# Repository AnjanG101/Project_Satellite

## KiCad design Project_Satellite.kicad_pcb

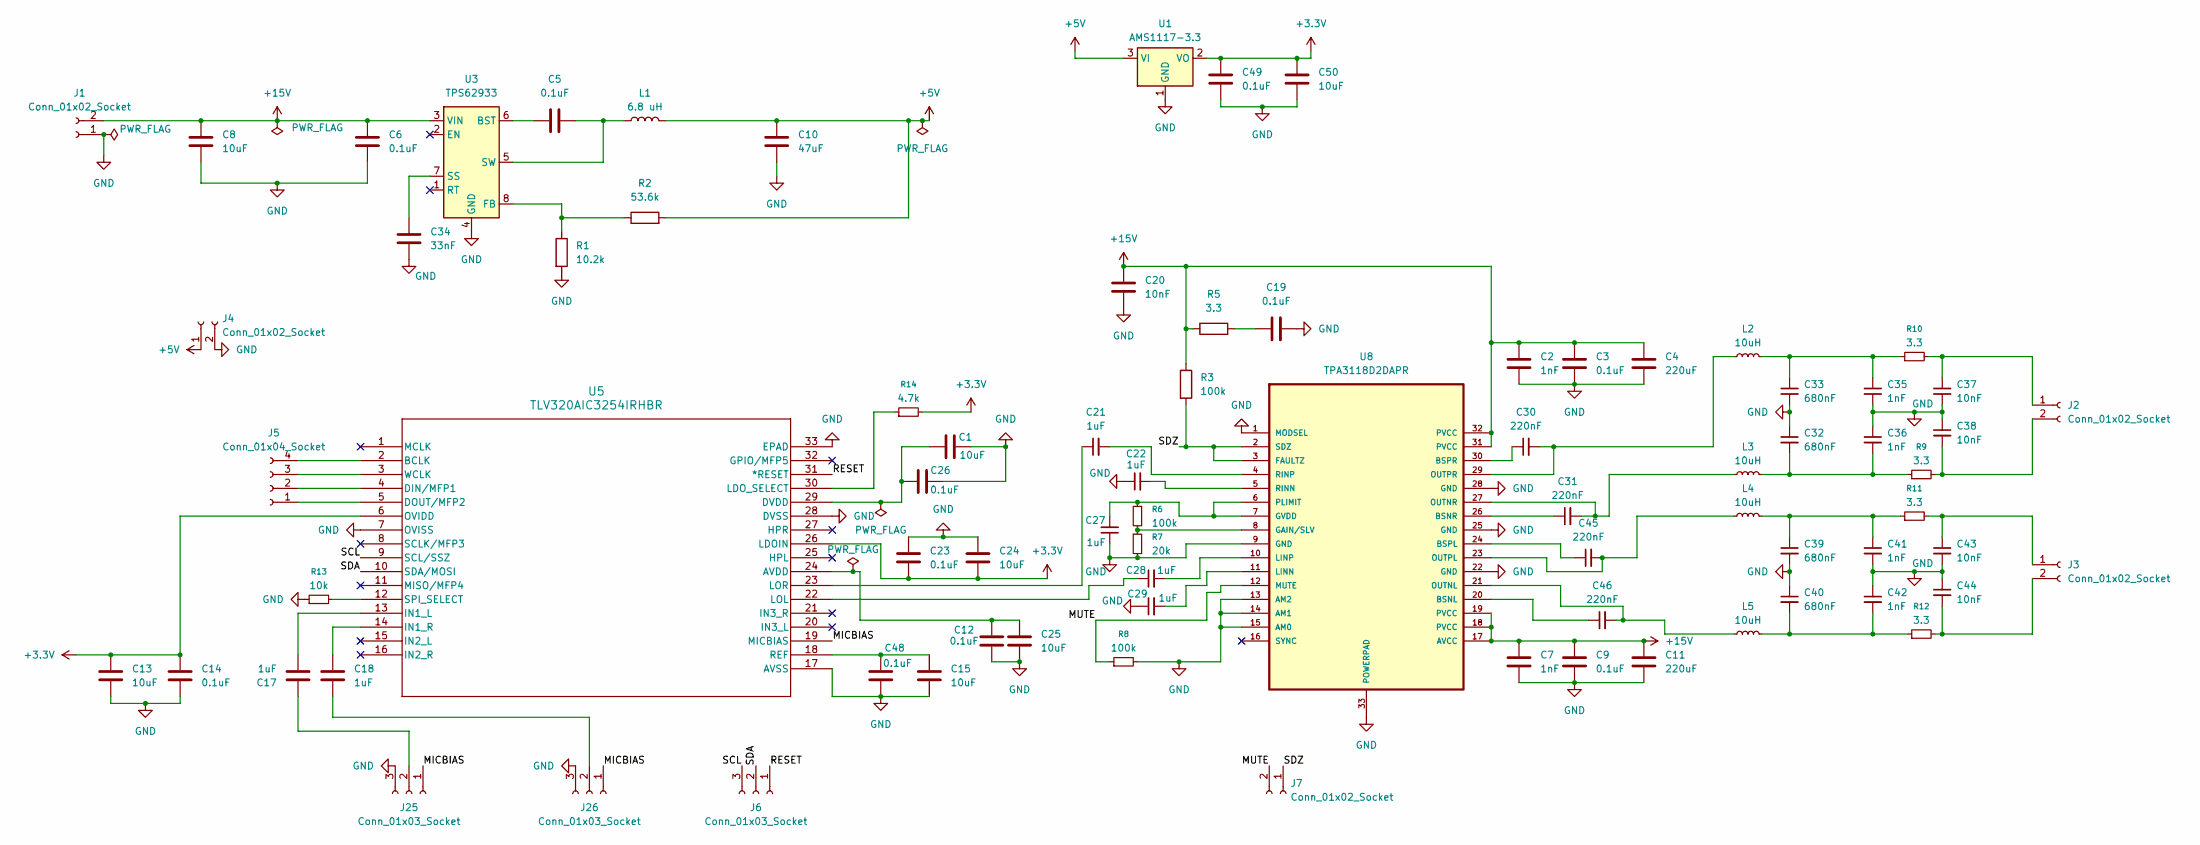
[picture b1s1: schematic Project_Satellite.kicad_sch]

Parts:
C1, C8, C13, C15, C24, C25, C50: 10uF; C_0805_2012Metric
C2, C7, C35, C36, C41, C42: 1nF; C_0402_1005Metric
C3, C5, C6, C9, C12, C14, C19, C23, C26, C48, C49: 0.1uF; C_0402_1005Metric
C4, C11: 220uF; CP_Radial_D5.0mm_P2.50mm
C10: 47uF; CP_Radial_D5.0mm_P2.50mm
C17, C18, C21, C22, C27, C28, C29: 1uF; C_0402_1005Metric
C20, C37, C38, C43, C44: 10nF; C_0402_1005Metric
C30, C31, C45, C46: 220nF; C_0402_1005Metric
C32, C33, C39, C40: 680nF; C_0603_1608Metric
C34: 33nF; C_0402_1005Metric
J1, J2, J3, J4, J7: Conn_01x02_Socket; JST_XH_B2B-XH-A_1x02_P2.50mm_Vertical
J5: Conn_01x04_Socket; JST_XH_B4B-XH-A_1x04_P2.50mm_Vertical
J6, J25, J26: Conn_01x03_Socket; JST_XH_B3B-XH-A_1x03_P2.50mm_Vertical
L1: 6.8 uH; L_APV_APH0630
L2, L3, L4, L5: 10uH; L_APV_APH0630
R1: 10.2k; C_0402_1005Metric
R2: 53.6k; C_0402_1005Metric
R3, R6, R8: 100k; C_0402_1005Metric
R5, R9, R10, R11, R12: 3.3; C_0402_1005Metric
R7: 20k; C_0402_1005Metric
R13: 10k; C_0402_1005Metric
R14: 4.7k; C_0402_1005Metric
U1: AMS1117-3.3
U3: TPS62933
U5: TLV320AIC3254IRHBR; TLV320AIC3254
U8: TPA3118D2DAPR; TPA3118

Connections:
+3.3V: C13.1, C14.1, C23.2, C24.2, C49.1, C50.1, R14.2, U1.2 (VO), U5.6 (OVIDD), U5.26 (LDOIN)
+5V: C10.1, J4.1, L1.2, R2.2, U1.3 (VI)
+15V: C2.1, C3.1, C4.1, C6.1, C7.1, C8.1, C9.1, C11.1, C20.1, J1.2, R3.1, R5.1, U3.3 (VIN), U8.17 (AVCC), U8.18 (PVCC), U8.19 (PVCC), U8.31 (PVCC), U8.32 (PVCC)
/MICBIAS: J25.1, J26.1, U5.19 (MICBIAS)
/MUTE: J7.2, R8.1, U8.12 (MUTE)
/RESET: J6.1, U5.31 (*RESET)
/SCL: J6.3, U5.9 (SCL/SSZ)
/SDA: J6.2, U5.10 (SDA/MOSI)
/SDZ: J7.1, R3.2, U8.2 (SDZ), U8.3 (FAULTZ)
GND: C1.2, C2.2, C3.2, C4.2, C6.2, C7.2, C8.2, C9.2, C10.2, C11.2, C12.2, C13.2, C14.2, C15.2, C19.2, C20.2, C22.1, C23.1, C24.1, C25.2, C26.2, C27.1, C29.1, C32.1, C33.2, C34.2, C35.2, C36.1, C37.2, C38.1, C39.2, C40.1, C41.2, C42.1, C43.2, C44.1, C48.1, C49.2, C50.2, J1.1, J4.2, J25.3, J26.3, R1.2, R7.2, R8.2, R13.1, U1.1 (GND), U3.4 (GND), U5.7 (OVISS), U5.17 (AVSS), U5.28 (DVSS), U5.33 (EPAD), U8.1 (MODSEL), U8.9 (GND), U8.13 (AM2), U8.14 (AM1), U8.15 (AM0), U8.22 (GND), U8.25 (GND), U8.28 (GND), U8.33 (POWERPAD)
unnamed: C19.1, R5.2
unnamed: C32.2, C36.2, L3.2, R9.1
unnamed: C33.1, C35.1, L2.2, R10.1
unnamed: C39.1, C41.1, L4.2, R11.1
unnamed: C40.2, C42.2, L5.2, R12.1
unnamed: C37.1, J2.1, R10.2
unnamed: C38.2, J2.2, R9.2
unnamed: C43.1, J3.1, R11.2
unnamed: C44.2, J3.2, R12.2
unnamed: J5.1, U5.5 (DOUT/MFP2)
unnamed: J5.2, U5.4 (DIN/MFP1)
unnamed: J5.3, U5.3 (WCLK)
unnamed: J5.4, U5.2 (BCLK)
unnamed: C17.1, J25.2
unnamed: C18.2, J26.2
unnamed: C5.1, U3.6 (BST)
unnamed: R1.1, R2.1, U3.8 (FB)
unnamed: C34.1, U3.7 (SS)
unnamed: C5.2, L1.1, U3.5 (SW)
unnamed: C12.1, C25.1, U5.24 (AVDD)
unnamed: C1.1, C26.1, U5.29 (DVDD)
unnamed: C17.2, U5.13 (IN1_L)
unnamed: C18.1, U5.14 (IN1_R)
unnamed: R14.1, U5.30 (LDO_SELECT)
unnamed: C28.1, U5.22 (LOL)
unnamed: C21.1, U5.23 (LOR)
unnamed: C15.1, C48.2, U5.18 (REF)
unnamed: R13.2, U5.12 (SPI_SELECT)
unnamed: C46.1, U8.20 (BSNL)
unnamed: C31.1, U8.26 (BSNR)
unnamed: C45.1, U8.24 (BSPL)
unnamed: C30.1, U8.30 (BSPR)
unnamed: R6.2, R7.1, U8.8 (GAIN/SLV)
unnamed: C27.2, R6.1, U8.6 (PLIMIT), U8.7 (GVDD)
unnamed: C29.2, U8.11 (LINN)
unnamed: C28.2, U8.10 (LINP)
unnamed: C46.2, L5.1, U8.21 (OUTNL)
unnamed: C31.2, L3.1, U8.27 (OUTNR)
unnamed: C45.2, L4.1, U8.23 (OUTPL)
unnamed: C30.2, L2.1, U8.29 (OUTPR)
unnamed: C22.2, U8.5 (RINN)
unnamed: C21.2, U8.4 (RINP)

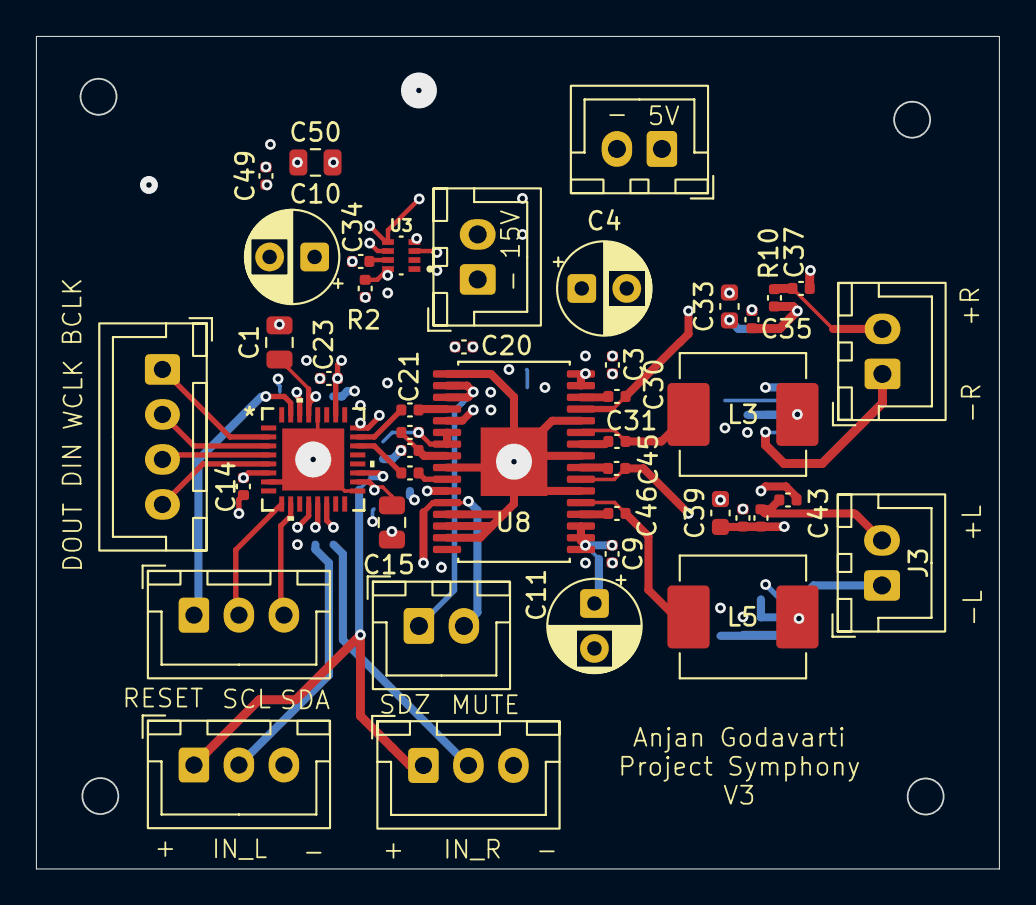
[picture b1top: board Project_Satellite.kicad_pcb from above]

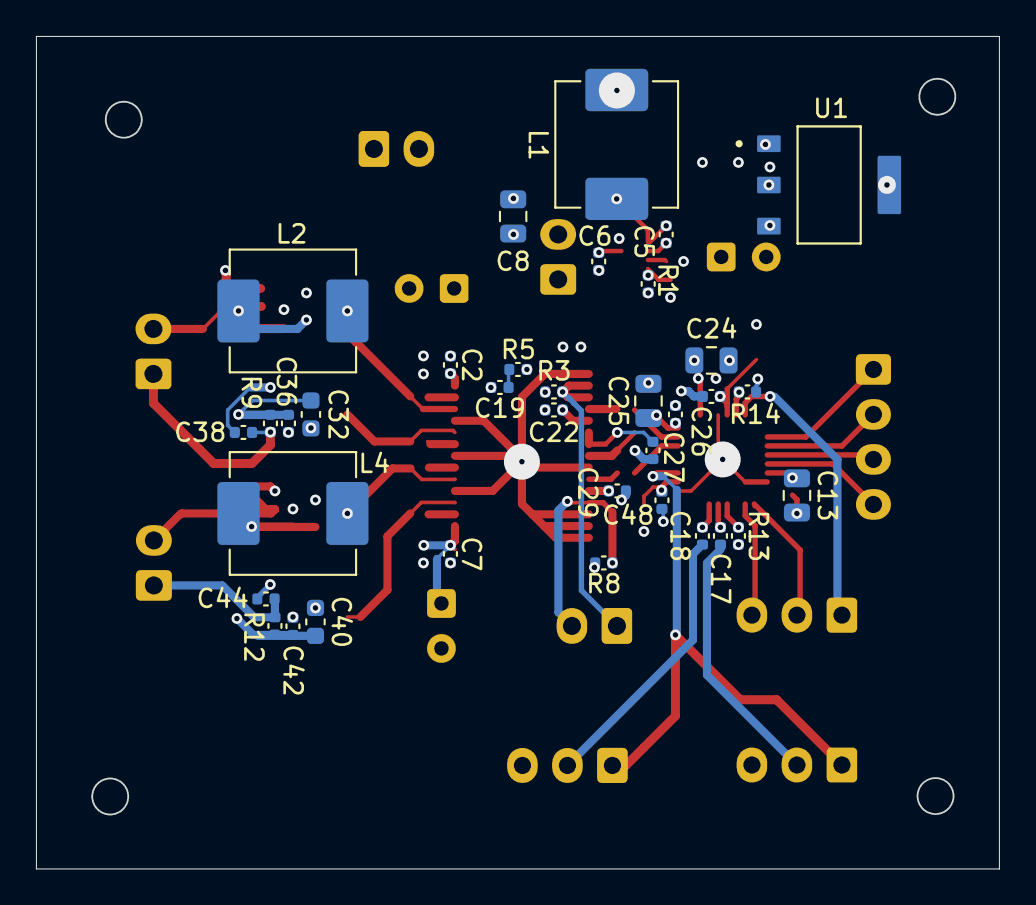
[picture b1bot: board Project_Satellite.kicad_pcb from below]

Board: 4 copper layers, 53.5 x 46.2 mm, 79 parts (35 on the bottom side), 52 nets.

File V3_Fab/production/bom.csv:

Designator,Footprint,Quantity,Value,LCSC Part #
"C1, C13, C15, C24, C25, C50, C8",0805,7,10uF,
C10,CP_Radial_D5.0mm_P2.50mm,1,47uF,
"C11, C4",CP_Radial_D5.0mm_P2.50mm,2,220uF,
"C12, C14, C19, C23, C26, C3, C48, C49, C5, C6, C9",0402,11,0.1uF,
"C17, C18, C21, C22, C27, C28, C29",0402,7,1uF,
"C2, C35, C36, C41, C42, C7",0402,6,1nF,
"C20, C37, C38, C43, C44",0402,5,10nF,
"C30, C31, C45, C46",0402,4,220nF,
"C32, C33, C39, C40",0603,4,680nF,
C34,0402,1,33nF,
"J1, J2, J3, J4, J7",JST_XH_B2B-XH-A_1x02_P2.50mm_Vertical,5,Conn_01x02_Socket,
"J25, J26, J6",JST_XH_B3B-XH-A_1x03_P2.50mm_Vertical,3,Conn_01x03_Socket,
J5,JST_XH_B4B-XH-A_1x04_P2.50mm_Vertical,1,Conn_01x04_Socket,
L1,L_APV_APH0630,1,6.8 uH,
"L2, L3, L4, L5",L_APV_APH0630,4,10uH,
R1,0402,1,10.2k,
"R10, R11, R12, R5, R9",0402,5,3.3,
R13,0402,1,10k,
R14,0402,1,4.7k,
R2,0402,1,53.6k,
"R3, R6, R8",0402,3,100k,
R7,0402,1,20k,
U1,AMS1117-3.3,1,AMS1117-3.3,
U3,TPS62933,1,TPS62933,
U5,TLV320AIC3254,1,TLV320AIC3254IRHBR,
U8,TPA3118,1,TPA3118D2DAPR,

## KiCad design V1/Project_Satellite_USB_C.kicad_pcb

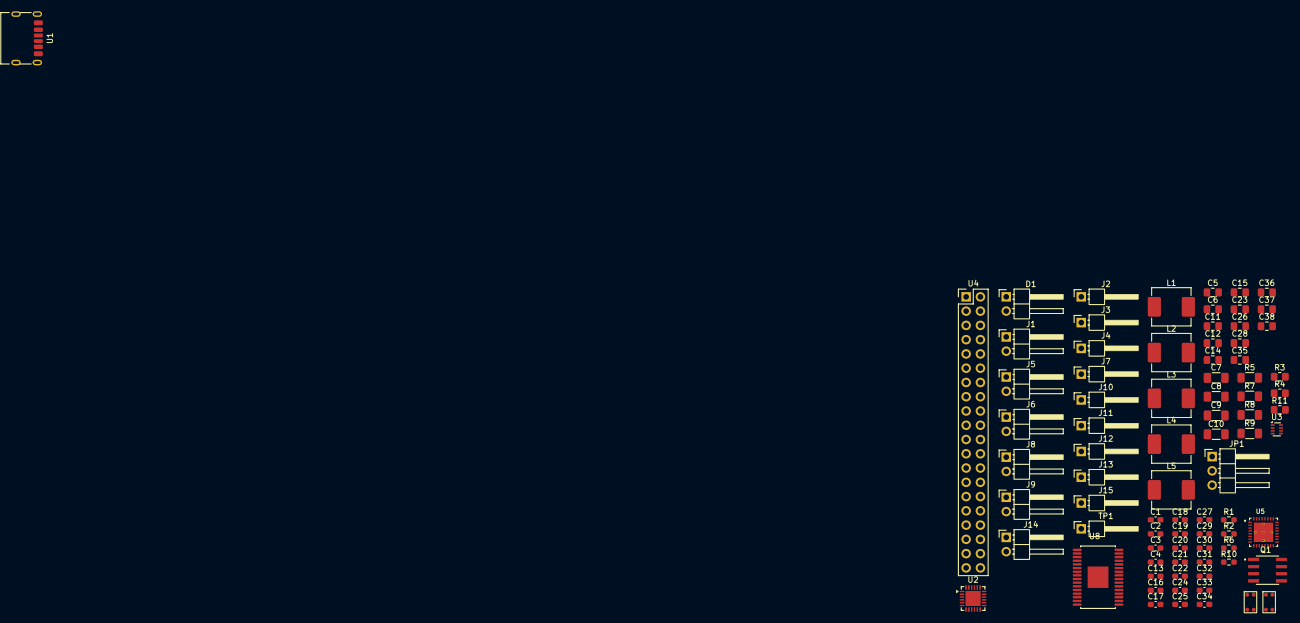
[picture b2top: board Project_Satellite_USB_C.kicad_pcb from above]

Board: 2 copper layers, 81 parts (0 on the bottom side), 67 nets, no tracks yet.

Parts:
C1, C2, C3, C13, C16, C17, C18, C24, C25, C27, C29: 1uF; C_0603_1608Metric_Pad1.08x0.95mm_HandSolder
C4: 4.7uF; C_0603_1608Metric_Pad1.08x0.95mm_HandSolder
C5, C6, C11, C12, C14, C15, C23, C26, C28: 0.1uF; C_0805_2012Metric_Pad1.18x1.45mm_HandSolder
C7, C8: 10uF; C_1206_3216Metric_Pad1.33x1.80mm_HandSolder
C9, C10: 22uF; C_1206_3216Metric_Pad1.33x1.80mm_HandSolder
C19, C20, C21, C22: 2.2uF; C_0603_1608Metric_Pad1.08x0.95mm_HandSolder
C30, C31, C32, C33: 220nF; C_0603_1608Metric_Pad1.08x0.95mm_HandSolder
C34: 33nF; C_0603_1608Metric_Pad1.08x0.95mm_HandSolder
C35, C36, C37, C38: 680nF; C_0805_2012Metric_Pad1.18x1.45mm_HandSolder
D1: LED; PinHeader_1x02_P2.54mm_Horizontal
J1, J5, J6, J8, J9, J14: Conn_01x02_Socket; PinHeader_1x02_P2.54mm_Horizontal
J2, J3, J4, J7, J10, J11, J12, J13, J15: Conn_01x01_Socket; PinHeader_1x01_P2.54mm_Horizontal
JP1: Jumper_3_Open; PinHeader_1x03_P2.54mm_Horizontal
L1: 6.8 uH; L_APV_APH0630
L2, L3, L4, L5: 10uH; L_APV_APH0630
Q1: PMOS; PMOS-AO4407A
R1: 10.2k; R_0603_1608Metric_Pad0.98x0.95mm_HandSolder
R2: 53.6k; R_0603_1608Metric_Pad0.98x0.95mm_HandSolder
R3: 50; R_0805_2012Metric_Pad1.20x1.40mm_HandSolder
R4: 220; R_0805_2012Metric_Pad1.20x1.40mm_HandSolder
R5, R7, R8, R9: 10k; R_1206_3216Metric_Pad1.30x1.75mm_HandSolder
R6: 5.6k; R_0603_1608Metric_Pad0.98x0.95mm_HandSolder
R10: 470; R_0603_1608Metric_Pad0.98x0.95mm_HandSolder
R11: 100k; R_0805_2012Metric_Pad1.20x1.40mm_HandSolder
TP1: TestPoint; PinHeader_1x01_P2.54mm_Horizontal
U1: USB-C; USB_C_Receptacle_HRO_TYPE-C-31-M-17
U2: STUSB4500QTR; QFN-24-1EP_4x4mm_P0.5mm_EP2.7x2.7mm
U3: TPS62933; SOT-583-8
U4: RASPBERRY_PI_ZERO_2_W; PinHeader_2x20_P2.54mm_Vertical
U5: TLV320AIC3254IRHBR; TLV320AIC3254
U6, U7: MEMSMic
U8: TPA3118D2DAPR; TPA3118

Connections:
+3.3V: C12.2, C13.1, C14.1, C23.2, C24.2, J12.1, R5.1, R7.2, R8.2, U4.1 (3V3_1), U4.17 (3V3_17), U5.6 (OVIDD), U5.26 (LDOIN), U5.30 (LDO_SELECT)
+5V: C9.1, C10.1, C11.1, L1.2, R3.2, R4.1, U4.2 (5V_2), U4.4 (5V_4)
+15V: C6.1, C7.1, C8.1, C28.2, C29.2, Q1.1 (D), U3.3 (VIN), U8.17 (AVCC), U8.18 (PVCC), U8.19 (PVCC), U8.31 (PVCC), U8.32 (PVCC)
/MICBIAS: U5.19 (MICBIAS), U6.2 (VDD), U7.2 (VDD)
GND: C1.1, C2.1, C3.1, C4.2, C6.2, C7.2, C8.2, C9.2, C10.2, C11.2, C12.1, C13.2, C14.2, C15.2, C16.2, C19.1, C21.1, C23.1, C24.1, C25.2, C26.1, C27.2, C28.1, C29.1, C34.2, C35.1, C36.1, C37.2, C38.2, D1.2 (A), J14.2, JP1.3 (B), R1.2, R6.1, R9.1, U1.0 (GND), U1.5 (GND), U2.10 (GND), U2.13 (ADDR1), U2.25 (GND), U3.4 (GND), U4.6 (GND_6), U4.9 (GND_9), U4.14 (GND_14), U4.20 (GND_20), U4.25 (GND_25), U4.30 (GND_30), U4.34 (GND_34), U4.39 (GND_39), U5.7 (OVISS), U5.12 (SPI_SELECT), U5.17 (AVSS), U5.28 (DVSS), U5.33 (EPAD), U6.3 (GND), U6.4 (GND), U7.3 (GND), U7.4 (GND), U8.1 (MODSEL), U8.9 (GND), U8.13 (AM2), U8.14 (AM1), U8.15 (AM0), U8.22 (GND), U8.25 (GND), U8.28 (GND), U8.33 (POWERPAD)
unnamed: D1.1 (K), R4.2
unnamed: J1.1, U2.8 (SDA)
unnamed: J1.2, U2.7 (SCL)
unnamed: J2.1, U2.19 (ALERT)
unnamed: J3.1, U2.11 (ATTACH)
unnamed: J4.1, U2.15 (GPIO)
unnamed: J5.1, U4.5 (GPIO3/SCL)
unnamed: J5.2, U4.3 (GPIO2/SDA1)
unnamed: J6.1, U5.10 (SDA/MOSI)
unnamed: J6.2, U5.9 (SCL/SSZ)
unnamed: J7.1, R5.2, U5.31 (*RESET)
unnamed: C35.2, J8.1, L2.2
unnamed: C36.2, J8.2, L3.2
unnamed: C37.1, J9.1, L4.2
unnamed: C38.1, J9.2, L5.2
unnamed: J10.1, U8.2 (SDZ)
unnamed: J11.1, U8.3 (FAULTZ)
unnamed: J13.1, R9.2, U2.6 (RESET)
unnamed: J14.1, JP1.1 (A)
unnamed: J15.1, U3.2 (EN)
unnamed: JP1.2 (C), U2.22 (VSYS)
unnamed: Q1.2 (G), R11.2, U2.16 (VBUS_EN_SNK)
unnamed: U1.2 (CC1), U2.1 (CC1DB), U2.2 (CC1)
unnamed: U1.3 (CC2), U2.4 (CC2), U2.5 (CC2DB)
unnamed: R8.1, U2.12 (ADDR0)
unnamed: R10.2, U2.18 (VBUS_VS_DISCH)
unnamed: C1.2, U2.21 (VREG_1V2)
unnamed: C2.2, U2.23 (VREG_2V7)
unnamed: C5.1, U3.6 (BST)
unnamed: R1.1, R2.1, R2.2, R3.1, U3.8 (FB)
unnamed: C34.1, U3.7 (SS)
unnamed: C5.2, L1.1, U3.5 (SW)
unnamed: U4.12 (GPIO18/GPIO_GEN1), U5.2 (BCLK)
unnamed: U4.35 (GPIO19), U5.3 (WCLK)
unnamed: U4.38 (GPIO20), U5.4 (DIN/MFP1)
unnamed: U4.40 (GPIO21), U5.5 (DOUT/MFP2)
unnamed: C25.1, U5.24 (AVDD)
unnamed: C26.2, U5.29 (DVDD)
unnamed: C17.2, U5.13 (IN1_L)
unnamed: C18.1, U5.14 (IN1_R)
unnamed: C20.1, U5.22 (LOL)
unnamed: C22.1, U5.23 (LOR)
unnamed: TP1.1, U5.1 (MCLK)
unnamed: C15.1, C16.1, U5.18 (REF)
unnamed: C17.1, U6.1 (Out)
unnamed: C18.2, U7.1 (Out)
unnamed: C30.2, U8.20 (BSNL)
unnamed: C31.1, U8.26 (BSNR)
unnamed: C32.1, U8.24 (BSPL)
unnamed: C33.1, U8.30 (BSPR)
unnamed: R6.2, U8.8 (GAIN/SLV)
unnamed: C27.1, U8.6 (PLIMIT), U8.7 (GVDD)
unnamed: C19.2, U8.11 (LINN)
unnamed: C20.2, U8.10 (LINP)
unnamed: R7.1, U8.12 (MUTE)
unnamed: C30.1, L2.1, U8.21 (OUTNL)
unnamed: C31.2, L3.1, U8.27 (OUTNR)
unnamed: C32.2, L4.1, U8.23 (OUTPL)
unnamed: C33.2, L5.1, U8.29 (OUTPR)
unnamed: C21.2, U8.5 (RINN)
unnamed: C22.2, U8.4 (RINP)
VBUS: C3.2, C4.1, Q1.3 (S), R10.1, R11.1, U1.1 (VBUS), U1.4 (VBUS), U2.24 (VDD)

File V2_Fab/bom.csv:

Designator,Footprint,Quantity,Value,LCSC Part #
"C1, C12, C14, C15, C23, C26, C28, C5, C6",0805,9,0.1uF,
C10,1206,1,47uF,
"C13, C16, C17, C18, C24, C25, C27, C29",0603,8,1uF,
"C19, C20, C21, C22",0603,4,2.2uF,
"C30, C31, C32, C33",0603,4,220nF,
C34,0603,1,33nF,
"C35, C36, C37, C38",0805,4,680nF,
C8,1206,1,10uF,
D1,LED_D3.0mm,1,LED,
"J1, J8, J9",JST_XH_B2B-XH-A_1x02_P2.50mm_Vertical,3,Conn_01x02_Socket,
"J25, J26, J27, J28",JST_XH_B3B-XH-A_1x03_P2.50mm_Vertical,4,Conn_01x03_Socket,
L1,L_APV_APH0630,1,6.8 uH,
"L2, L3, L4, L5",L_APV_APH0630,4,10uH,
R1,0603,1,10.2k,
R2,0603,1,53.6k,
R4,0805,1,220,
R6,0603,1,5.6k,
"TP1, TP2, TP3, TP4, TP5",TestPoint_Pad_D1.0mm,5,TestPoint,
U3,SOT-583-8,1,TPS62933,
U4,PinSocket_2x20_P2.54mm_Vertical,1,RASPBERRY_PI_ZERO_2_W,
U5,TLV320AIC3254,1,TLV320AIC3254IRHBR,
"U6, U7",MEMSMic,2,MEMSMic,
U8,TPA3118,1,TPA3118D2DAPR,
